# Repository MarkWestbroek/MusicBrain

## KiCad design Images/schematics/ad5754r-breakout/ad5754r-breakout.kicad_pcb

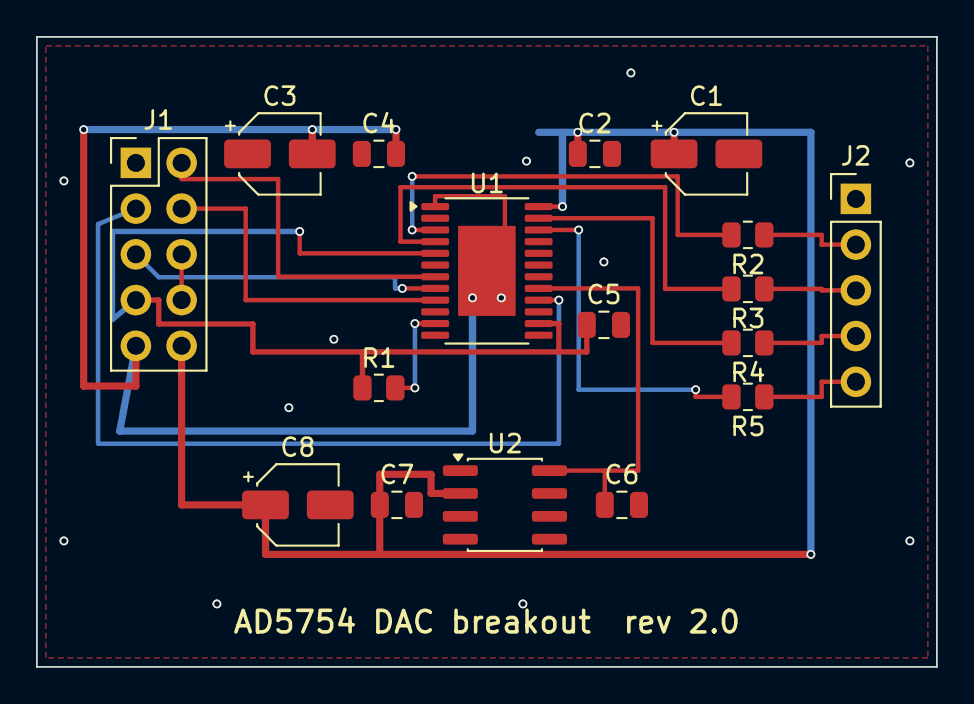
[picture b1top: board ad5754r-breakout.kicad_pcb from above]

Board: 2 copper layers, 50.0 x 35.0 mm, 17 parts (0 on the bottom side), 18 nets.

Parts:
C1, C3, C8: 10uF/25V; CP_Elec_4x5.3
C2, C4, C5, C6, C7: 100nF; C_0805_2012Metric
J1: SPI+Power; PinHeader_2x05_P2.54mm_Vertical
J2: GND+DAC A-D; PinHeader_1x05_P2.54mm_Vertical
R1: 10k; R_0805_2012Metric
R2, R3, R4, R5: 100R; R_0805_2012Metric
U1: AD5754BREZ; HTSSOP-24-1EP_4.4x7.8mm_P0.65mm_EP3.2x5mm
U2: ADR421; SOIC-8_3.9x4.9mm_P1.27mm

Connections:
+3V3: C5.1, J1.7, R1.1, U1.5, U1.14
+12V: C1.1, C2.1, C7.1, C8.1, J1.10, U1.24, U2.2
-12V: C3.2, C4.2, J1.9, U1.1, U1.25
/SCLK: J1.5, U1.8
/SDIN: J1.4, U1.9
/SDO: J1.3, U1.16
/SYNC: J1.2, U1.7
/VOUTA: R2.2, U1.3
/VOUTB: R3.2, U1.4
/VOUTC: R4.2, U1.23
/VOUTD: R5.2, U1.22
/VREF: C6.1, U1.17, U2.8
GND: C1.2, C2.2, C3.1, C4.1, C5.2, C6.2, C7.2, C8.2, J1.1, J1.6, J1.8, J2.1, U1.10, U1.15, U1.18, U1.19, U1.20, U1.21, U2.4
unnamed: J2.2, R2.1
unnamed: J2.3, R3.1
unnamed: J2.4, R4.1
unnamed: J2.5, R5.1
unnamed: R1.2, U1.11

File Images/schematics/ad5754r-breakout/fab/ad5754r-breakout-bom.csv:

"Comment","Designator","Footprint","Qty","LCSC Part #"
"10uF/25V","C1,C3,C8","Capacitor_SMD:CP_Elec_4x5.3","3",""
"100nF","C2,C4-C7","Capacitor_SMD:C_0805_2012Metric","5",""
"SPI+Power","J1","Connector_PinHeader_2.54mm:PinHeader_2x05_P2.54mm_Vertical","1",""
"GND+DAC A-D","J2","Connector_PinHeader_2.54mm:PinHeader_1x05_P2.54mm_Vertical","1",""
"10k","R1","Resistor_SMD:R_0805_2012Metric","1",""
"100R","R2-R5","Resistor_SMD:R_0805_2012Metric","4",""
"AD5754BREZ","U1","Package_SO:HTSSOP-24-1EP_4.4x7.8mm_P0.65mm_EP3.2x5mm","1",""
"ADR421","U2","Package_SO:SOIC-8_3.9x4.9mm_P1.27mm","1",""

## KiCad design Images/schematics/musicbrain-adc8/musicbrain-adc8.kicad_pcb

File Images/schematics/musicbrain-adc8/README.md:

# MusicBrain ADC8 — 8× CV-ingang (slotkaart)

**Status**: v1.1 — schema ERC-schoon + netlist geverifieerd; PCB **volledig
geroute** (DRC 0 fouten, 0 unconnected).
**Spec**: `doc/spi-bus-spec.md`. Bord: 40 mm breed × **80 mm hoog**
(standaard-kaarthoogte H voor de gedeelde bovenplaat), 2 lagen.

## Wat het is

8 CV-ingangen op een **AD7606** (16-bit SAR, 8 kanalen simultaan gesampled):
±10V of ±5V **rechtstreeks de chip in** — 1 MΩ ingangsimpedantie en interne
clamps, dus géén opamp-frontend per kanaal. Keuze overgenomen van Nic
Newdigate's teensy-eurorack-breakout (met toestemming); de pinout is tegen
zijn bewezen ontwerp geverifieerd.

## Busaansluiting (seriële mode)

| AD7606 | Buslijn | Toelichting |
|---|---|---|
| ~RD/SCLK, ~CS | SCLK, CS | seriële uitlezing |
| DOUTA | MISO | 8×16 bit achter elkaar; DOUTB ongebruikt (nc) |
| CONVST A+B (gekoppeld) | **SPARE1 = CONVST** | busbrede "sample nú"-strobe — alle ADC-kaarten samplen synchroon |
| BUSY | IRQ (slotpin 16) | hoog tijdens conversie (~4 µs); dalende flank = data klaar → interrupt |
| RESET | **SPARE2 = ADC_RESET** | resetpuls na power-up, firmware-gestuurd; 100k pulldown (R9) op de kaart |
| PAR/~SER, ~STBY, REF_SELECT | +3V3 | serieel, actief, interne 2,5V-referentie |
| RANGE | JP1 | jumper: +3V3 = ±10V, GND = ±5V |
| OS0..2, DB0-6, DB9-15 | GND | geen oversampling; parallelle databus plat |

Firmware-cyclus: CONVST-puls → wacht op IRQ (BUSY↓) → CS laag → 8×16 bit
klokken via MISO → CS hoog.

## Voeding & ondersteuning

- AVCC = 5V **lokaal** (AMS1117-5.0 uit +12V, zoals op de gate-kaart);
  VDRIVE = +3V3 van de bus, zodat de logica op busniveau praat.
- REGCAP ×2 (1 µF), REFCAPA/B gekoppeld (10 µF), REFIN/REFOUT (10 µF) —
  de voorgeschreven ondersteuning voor de interne referentie.
- 1 kΩ serie in alle acht ingangen (bescherming); VxGND-pinnen aan het
  GND-vlak.

## Aansluitingen

- **J1** (haakse male 2×10, onderrand): bus-slotcontract; MOSI/LDAC/SDA/SCL nc.
- **J2** (haakse male 1×10, bovenrand, recht boven het midden van J1):
  1 = GND, 2–9 = IN1..8, 10 = GND — **identiek contract als GATE8-J2**,
  dus hetzelfde jack8-printje past.
- **JP1** (1×3): RANGE-keuze ±10V / ±5V.

## PCB-notities (v1.1)

De volgorde-omkering tussen de chip-ingangen (V1 oost … V8 west op de
noordrij) en het J2-contract (IN1 west … IN8 oost) is opgelost met
**Manhattan-routing**: F.Cu draagt uitsluitend verticalen (escape onder elk
V-pad, drop naar elke serieweerstand), B.Cu draagt acht horizontale lanes
(y 118,4–124,0, steek 0,8 mm) — zo kruist niets op dezelfde laag. De
SPI/stuur-lijnen bereiken de westkolom van de chip via zes F-verticalen
("diepste entry → oostelijkste verticaal"), gevoed vanaf J1 via korte
B-lanes onderin. De GND-pads tussen de V-escapes hangen aan een eigen
verzamelrail (y 130,5) met via's naar het B-vlak.

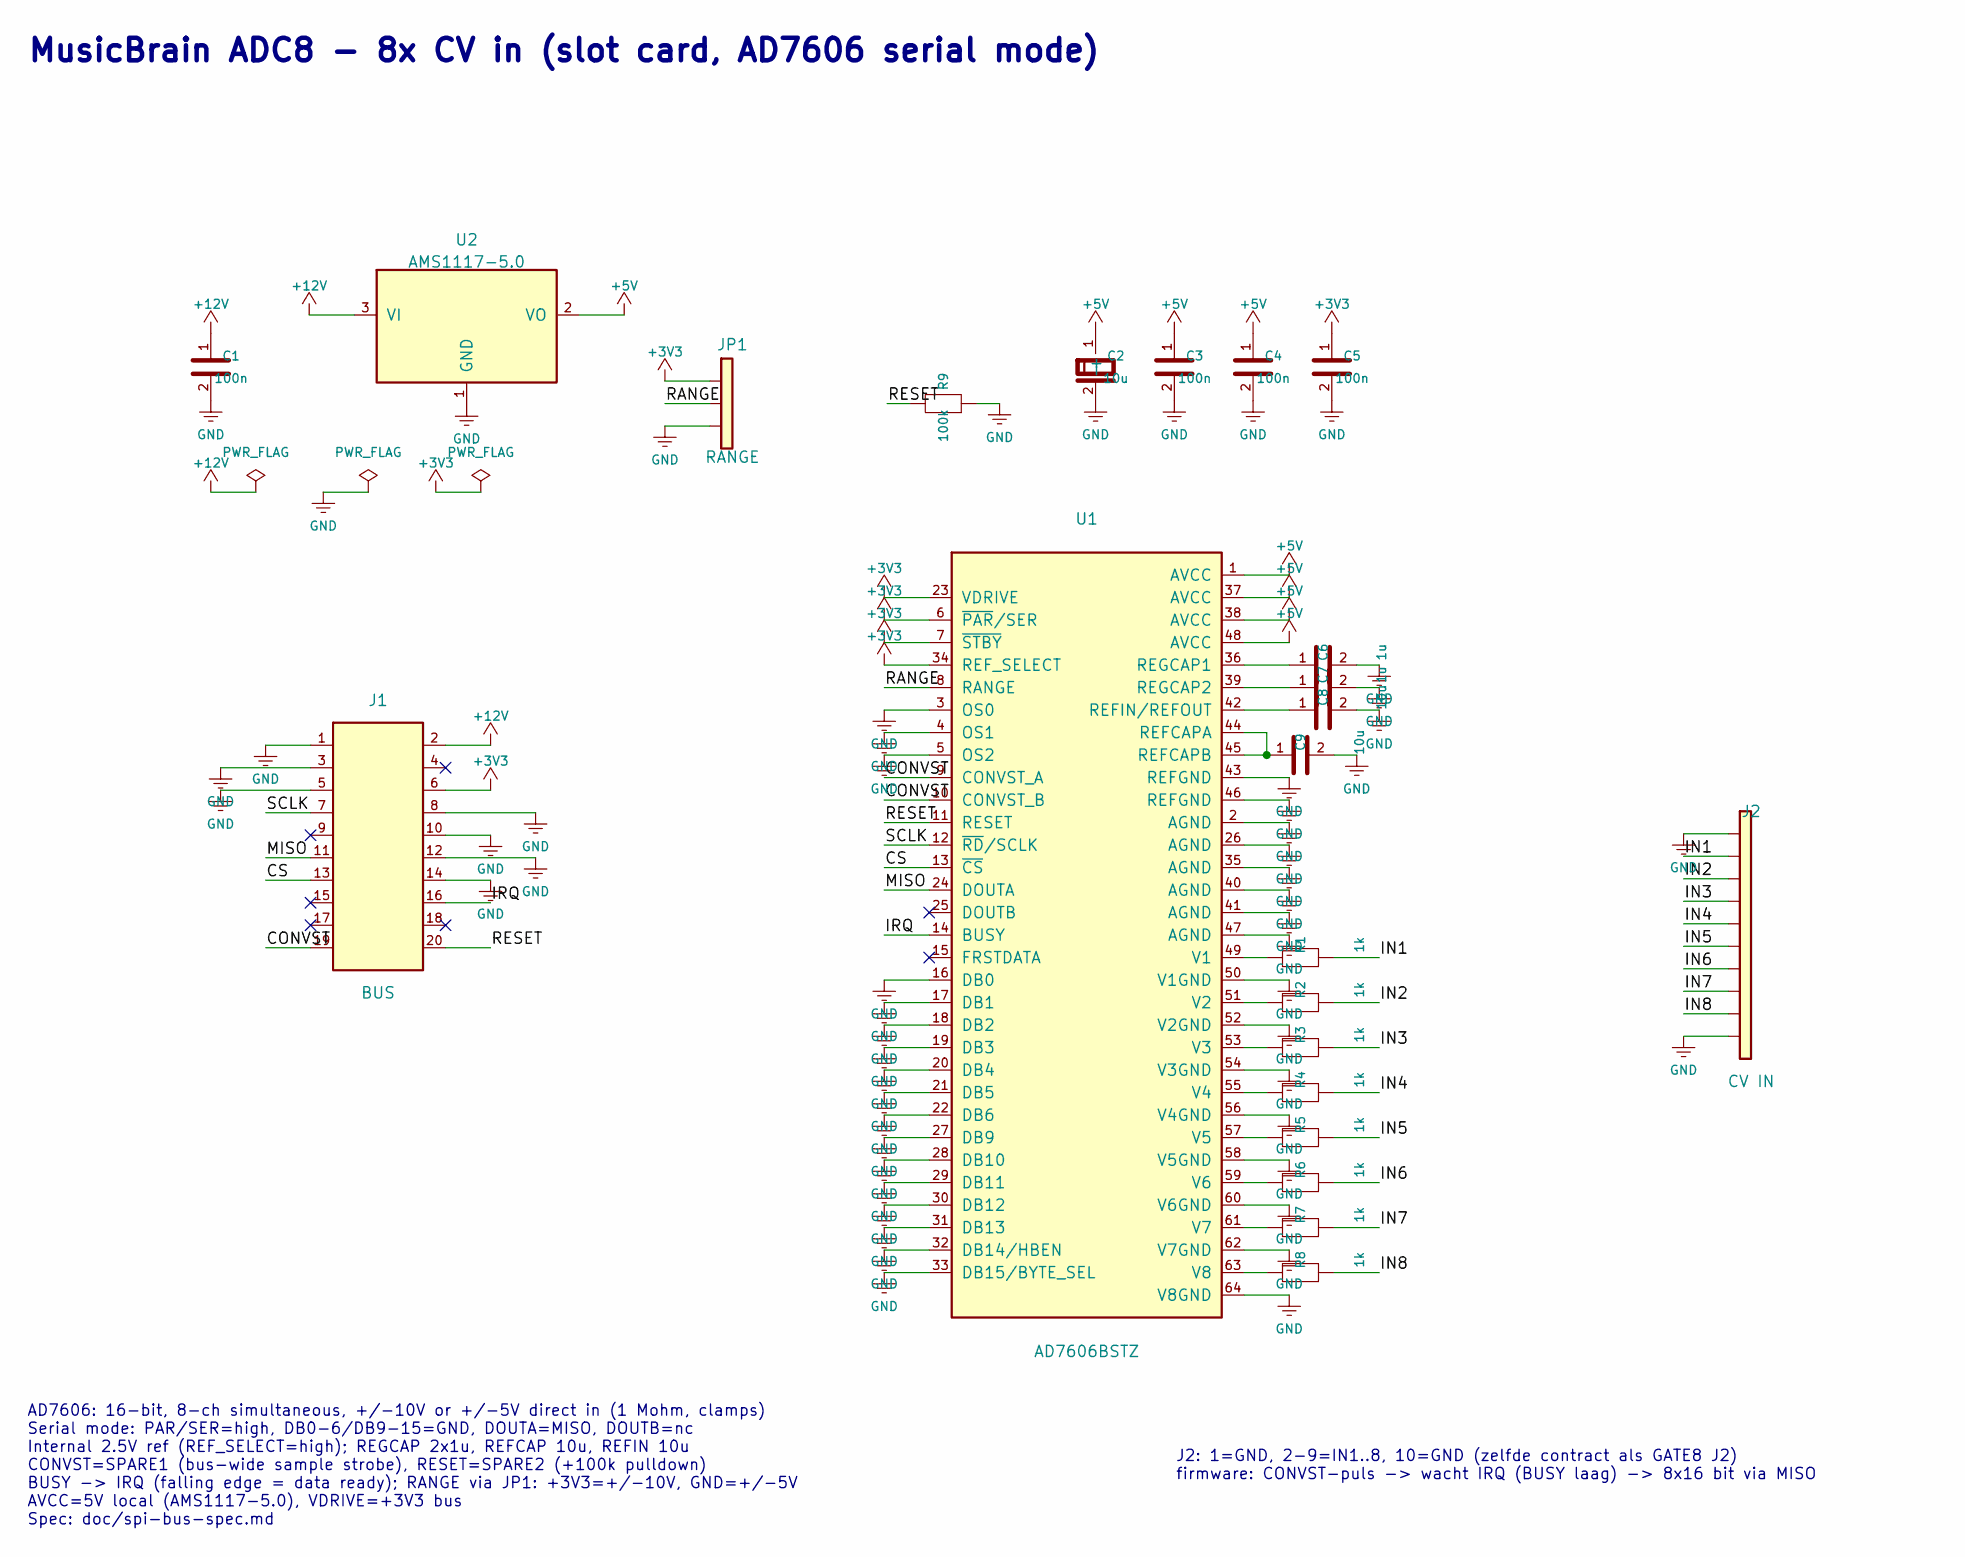
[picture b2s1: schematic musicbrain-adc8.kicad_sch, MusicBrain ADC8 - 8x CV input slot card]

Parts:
C1, C3, C4, C5: 100n; C_0805_2012Metric
C2: 10u; CP_Elec_4x5.3
C6, C7: 1u; C_0805_2012Metric
C8, C9: 10u; C_0805_2012Metric
J1: BUS; PinHeader_2x10_P2.54mm_Horizontal
J2: CV IN; PinHeader_1x10_P2.54mm_Horizontal
JP1: RANGE; PinHeader_1x03_P2.54mm_Vertical
R1, R2, R3, R4, R5, R6, R7, R8: 1k; R_0805_2012Metric
R9: 100k; R_0805_2012Metric
U1: AD7606BSTZ; LQFP-64_10x10mm_P0.5mm
U2: AMS1117-5.0; SOT-223-3_TabPin2

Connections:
+3V3: C5.1, J1.6, JP1.1, U1.6 (~PAR/SER), U1.7 (~STBY), U1.23 (VDRIVE), U1.34 (REF_SELECT)
+5V: C2.1 (+), C3.1, C4.1, U1.1 (AVCC), U1.37 (AVCC), U1.38 (AVCC), U1.48 (AVCC), U2.2 (VO)
+12V: C1.1, J1.2, U2.3 (VI)
/CONVST: J1.19, U1.9 (CONVST_A), U1.10 (CONVST_B)
/CS: J1.13, U1.13 (~CS)
/IN1: J2.2, R1.2
/IN2: J2.3, R2.2
/IN3: J2.4, R3.2
/IN4: J2.5, R4.2
/IN5: J2.6, R5.2
/IN6: J2.7, R6.2
/IN7: J2.8, R7.2
/IN8: J2.9, R8.2
/IRQ: J1.16, U1.14 (BUSY)
/MISO: J1.11, U1.24 (DOUTA)
/RANGE: JP1.2, U1.8 (RANGE)
/RESET: J1.20, R9.1, U1.11 (RESET)
/SCLK: J1.7, U1.12 (~RD/SCLK)
GND: C1.2, C2.2 (-), C3.2, C4.2, C5.2, C6.2, C7.2, C8.2, C9.2, J1.1, J1.3, J1.5, J1.8, J1.10, J1.12, J1.14, J2.1, J2.10, JP1.3, R9.2, U1.2 (AGND), U1.3 (OS0), U1.4 (OS1), U1.5 (OS2), U1.16 (DB0), U1.17 (DB1), U1.18 (DB2), U1.19 (DB3), U1.20 (DB4), U1.21 (DB5), U1.22 (DB6), U1.26 (AGND), U1.27 (DB9), U1.28 (DB10), U1.29 (DB11), U1.30 (DB12), U1.31 (DB13), U1.32 (DB14/HBEN), U1.33 (DB15/BYTE_SEL), U1.35 (AGND), U1.40 (AGND), U1.41 (AGND), U1.43 (REFGND), U1.46 (REFGND), U1.47 (AGND), U1.50 (V1GND), U1.52 (V2GND), U1.54 (V3GND), U1.56 (V4GND), U1.58 (V5GND), U1.60 (V6GND), U1.62 (V7GND), U1.64 (V8GND), U2.1 (GND)
unnamed: C9.1, U1.44 (REFCAPA), U1.45 (REFCAPB)
unnamed: C8.1, U1.42 (REFIN/REFOUT)
unnamed: C6.1, U1.36 (REGCAP1)
unnamed: C7.1, U1.39 (REGCAP2)
unnamed: R1.1, U1.49 (V1)
unnamed: R2.1, U1.51 (V2)
unnamed: R3.1, U1.53 (V3)
unnamed: R4.1, U1.55 (V4)
unnamed: R5.1, U1.57 (V5)
unnamed: R6.1, U1.59 (V6)
unnamed: R7.1, U1.61 (V7)
unnamed: R8.1, U1.63 (V8)

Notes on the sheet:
MusicBrain ADC8 - 8x CV in (slot card, AD7606 serial mode)
AD7606: 16-bit, 8-ch simultaneous, +/-10V or +/-5V direct in (1 Mohm, clamps) Serial mode: PAR/SER=high, DB0-6/DB9-15=GND, DOUTA=MISO, DOUTB=nc Internal 2.5V ref (REF_SELECT=high); REGCAP 2x1u, REFCAP 10u, REFIN 10u CONVST=SPARE1 (bus-wide sample strobe), RESET=SPARE2 (+100k pulldown) BUSY -> IRQ (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
J2: 1=GND, 2-9=IN1..8, 10=GND (zelfde contract als GATE8 J2) firmware: CONVST-puls -> wacht IRQ (BUSY laag) -> 8x16 bit via MISO

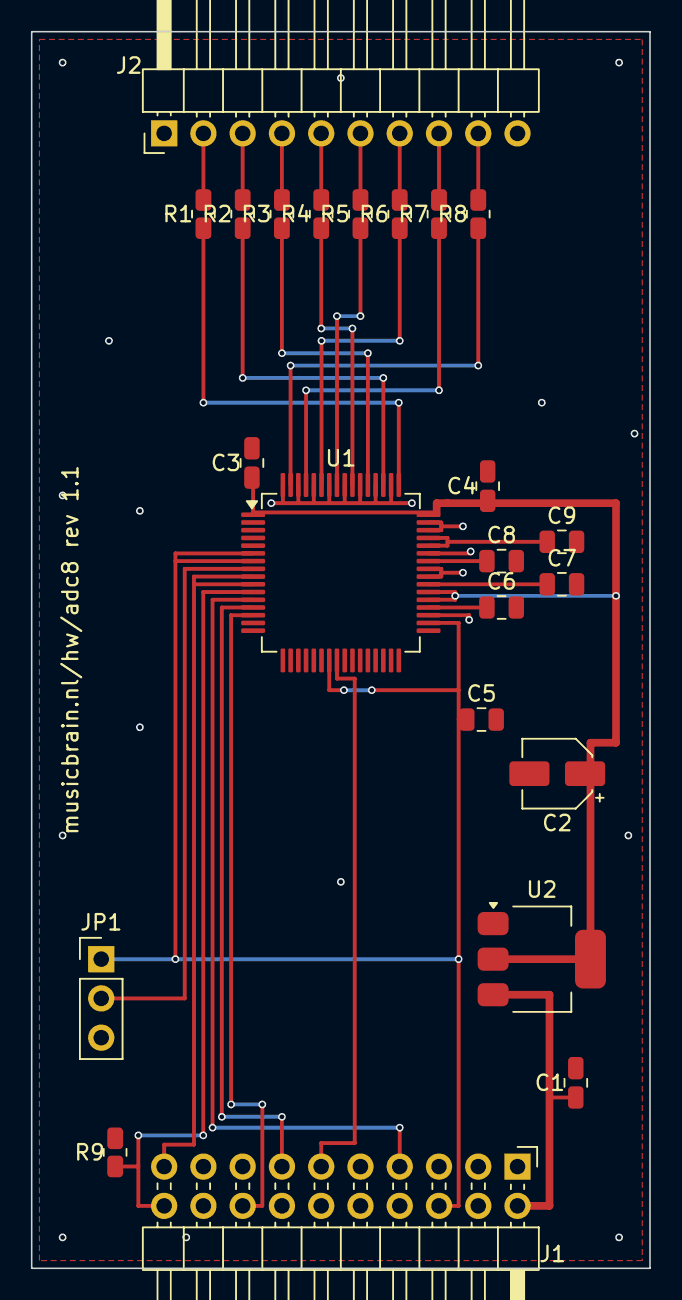
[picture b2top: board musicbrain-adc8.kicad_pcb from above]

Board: 2 copper layers, 40.0 x 80.0 mm, 23 parts (0 on the bottom side), 31 nets.

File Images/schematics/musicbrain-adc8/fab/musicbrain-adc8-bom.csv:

"Comment","Designator","Footprint","Qty","LCSC Part #"
"100n","C1,C3-C5","Capacitor_SMD:C_0805_2012Metric","4",""
"10u","C2","Capacitor_SMD:CP_Elec_4x5.3","1",""
"1u","C6,C7","Capacitor_SMD:C_0805_2012Metric","2",""
"10u","C8,C9","Capacitor_SMD:C_0805_2012Metric","2",""
"BUS","J1","Connector_PinHeader_2.54mm:PinHeader_2x10_P2.54mm_Horizontal","1",""
"CV IN","J2","Connector_PinHeader_2.54mm:PinHeader_1x10_P2.54mm_Horizontal","1",""
"RANGE","JP1","Connector_PinHeader_2.54mm:PinHeader_1x03_P2.54mm_Vertical","1",""
"1k","R1-R8","Resistor_SMD:R_0805_2012Metric","8",""
"100k","R9","Resistor_SMD:R_0805_2012Metric","1",""
"AD7606BSTZ","U1","Package_QFP:LQFP-64_10x10mm_P0.5mm","1",""
"AMS1117-5.0","U2","Package_TO_SOT_SMD:SOT-223-3_TabPin2","1",""

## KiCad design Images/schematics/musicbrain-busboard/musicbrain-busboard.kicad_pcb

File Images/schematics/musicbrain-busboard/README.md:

# MusicBrain busboard — Teensy 4.1 backplane

**Status**: schema ERC-schoon; PCB volledig geroute (DRC 0 fouten, 0 unconnected).
**Leidende spec**: `doc/spi-bus-spec.md`. Bestanden: `.kicad_sch` / `.kicad_pcb`, PDF's ernaast.

## Wat het is

De ruggengraat van het systeem: een 200×115 mm backplane met een Teensy 4.1
(op twee 1×24 socketstrips), **6 verticale kaartslots** (2×10 pinsocket) en
**2 hub-headers** (2×5 IDC) waar bestaande breakouts via lintkabel op
aansluiten. Voeding komt binnen als Eurorack ±12V; het bord maakt daar zelf
+5V (R-78E5.0 buck) en +3V3 (AMS1117) van.

## Signaalarchitectuur

| Groep | Lijnen | Teensy-pin | Toelichting |
|---|---|---|---|
| SPI | SCLK / MOSI / MISO | 13 / 11 / 12 | gedeeld door alle slots + hubs; slaves laten MISO los als hun CS hoog is |
| Chip-selects | CS1..CS6 → slot 1..6 | 10, 9, 8, 7, 6, 5 | **directe GPIO's**, één per slot ("geografisch": elke kaart ziet zijn CS op connectorpin 13) |
| | CS7, CS8 → hub 1, 2 | 4, 3 | vast bedraad naar pin 2 (SYNC) van de hub-headers |
| Interrupts | IRQ1..IRQ6 → slot 1..6 | 28..33 | directe GPIO-ingangen, interrupt-capable; kaart meldt "data klaar" op connectorpin 16 |
| Sync-strobes | LDAC | 2 | alle DAC-kaarten updaten hun uitgangen tegelijk op LDAC↓ |
| | SPARE1 (= CONVST) | 40 | alle ADC-kaarten samplen tegelijk (spiegelbeeld van LDAC) |
| | SPARE2 (= ADC_RESET) | 41 | busbrede reset voor AD7606-kaarten; vrij voor andere kaarten |
| I2C | SDA / SCL | 18 / 19 | voor trage kaarten (pots/encoders/OLED); pull-ups 2k2 op het busboard |
| Voeding | +12V / −12V / +3V3 | — | +3V3 komt van de AMS1117, **niet** van de Teensy-regulator |

Signaalintegriteit: **33 Ω serieweerstanden (R1/R2) in SCLK en MOSI**, direct
bij de Teensy — serieterminatie die reflecties op de multidrop-bus dempt.
Start de firmware op 2–4 MHz SPI; opvoeren kan daarna.

## PCB-opbouw (hoe de routing in elkaar zit)

- **B.Cu (onderlaag): 28 horizontale "buslanen"** op y = 68…104,5 mm — van
  boven naar beneden: LDAC, MOSI, MISO, SCLK, SDA, SCL, SPARE1, SPARE2,
  +3V3 (0,5 mm), +12V en −12V (0,8 mm), +5V, dan CS1..CS8 en IRQ1..IRQ6.
  CS/IRQ-lanen lopen alleen zo ver oostwaarts als hun slot — daar zie je de
  "trappetjes" in de PDF.
- **F.Cu (bovenlaag): verticale aftakkingen.** Elk slot heeft rechts een eigen
  kanaal (13 sporen op 1 mm steek) dat de connectorpinnen via een via op de
  juiste laan prikt. De Teensy heeft links zijn eigen fan-out (26 signalen);
  de volgorde van de verticalen is zo gekozen dat niets elkaar kruist.
- **Hubs**: J7 (noord) waaiert naar beneden zijn lanen op, J8 (zuid) naar
  boven; J8 zit bewust onder de lanenbundel — zo blijft alles kruisingsvrij.
- **Voeding**: de ±12V van J9 steekt op F.Cu tussen de Teensy-padrijen door
  ("mid-rij-oversteek") naar de +12V/−12V-lanen; de +5V loopt als aparte laan
  van Teensy-VIN en de R-78E naar de ontkoppelrij (C1–C8, onderrand).
- **GND**: geen sporen — massieve vlakken op beide lagen (solid connect),
  15 stitching-via's.

## Aandachtspunten

- **Teensy VIN hangt aan de +5V-rail.** Wil je USB en busvoeding tegelijk:
  snij de VUSB/VIN-brug op de Teensy door (standaard PJRC-advies).
- De Teensy-footprint is custom (`MusicBrain:Teensy41_THT`): 48 THT-pads,
  0,6" rijafstand, nummering tegen de klok in — pin 1 linksboven bij de USB.
- Slots zijn PinSocket 2×10 (female); kaarten hebben male headers. Let op:
  de socket-footprint spiegelt kolom 2 naar links.
- Hot-pluggen van kaarten: niet doen (ongebufferde bus).

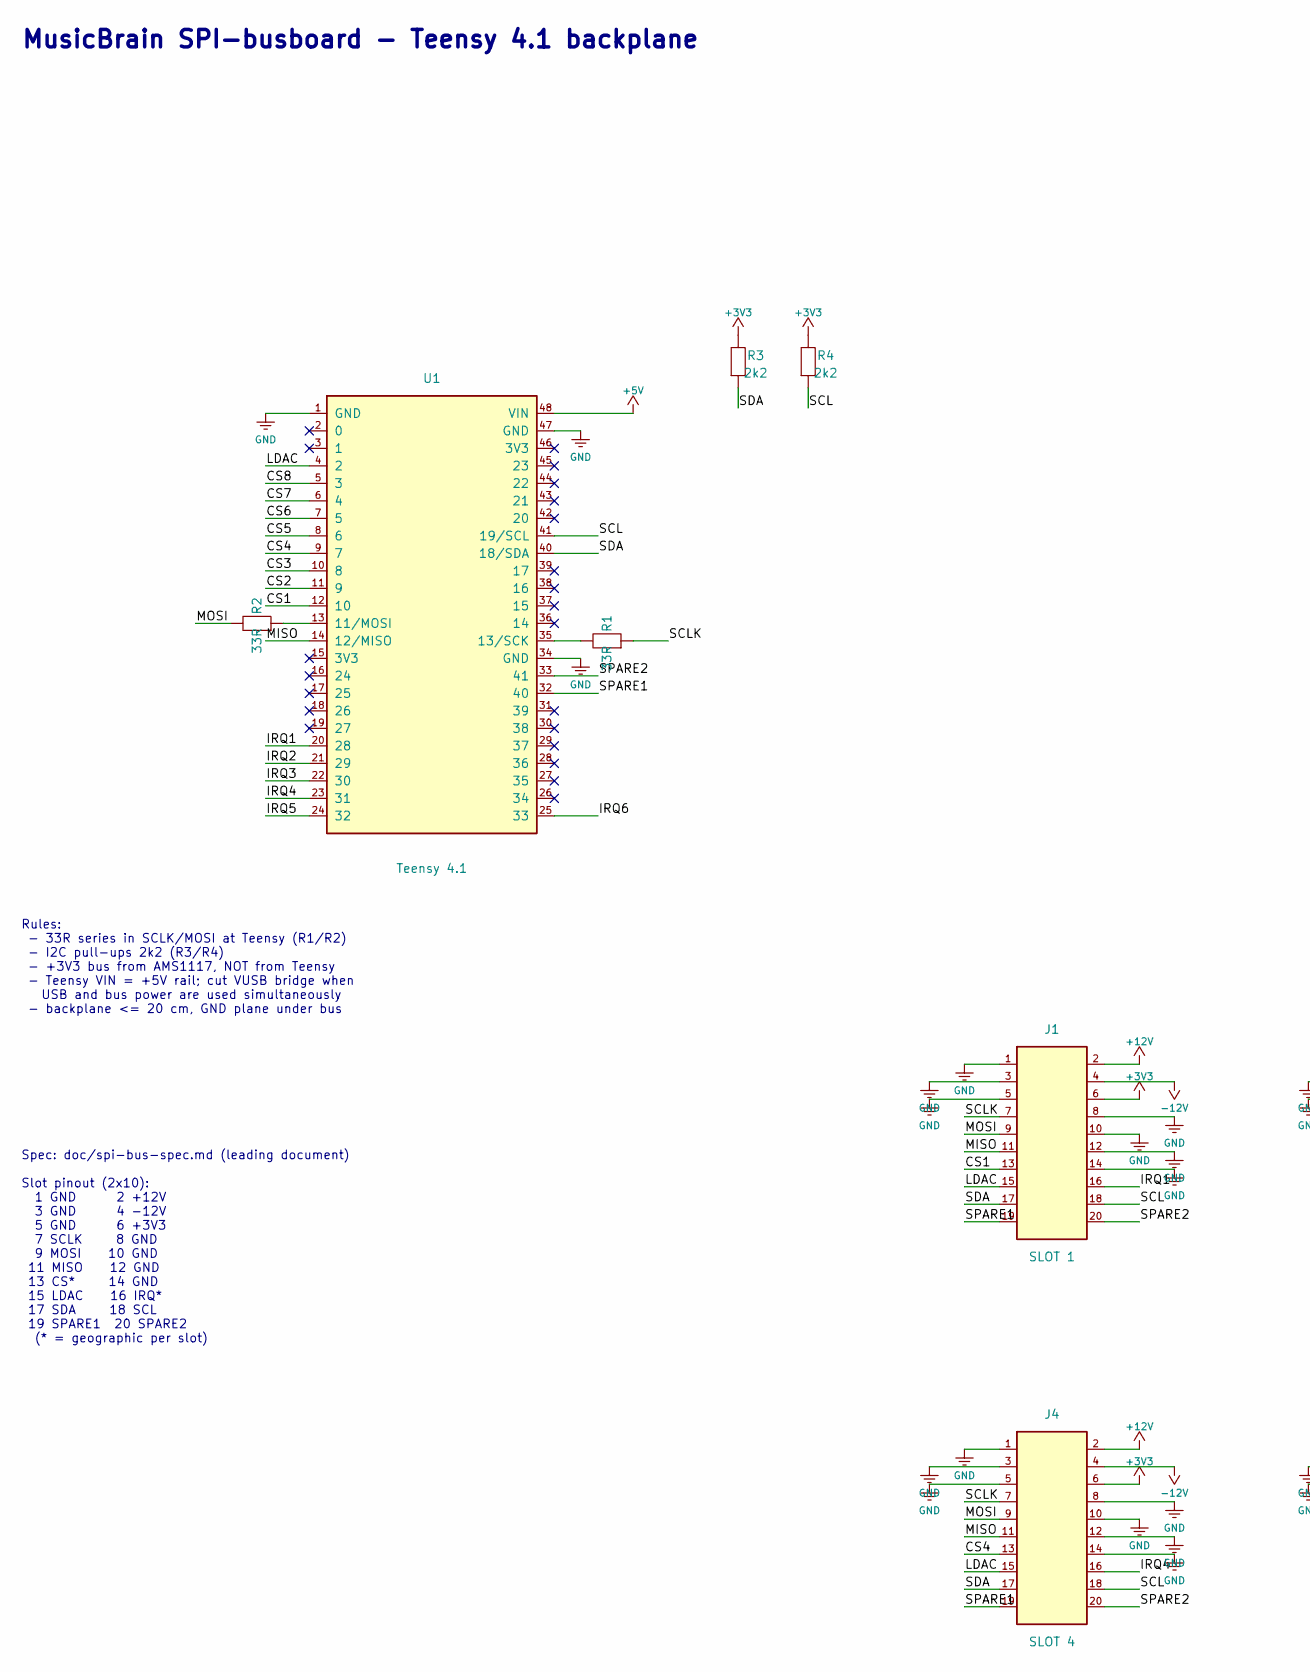
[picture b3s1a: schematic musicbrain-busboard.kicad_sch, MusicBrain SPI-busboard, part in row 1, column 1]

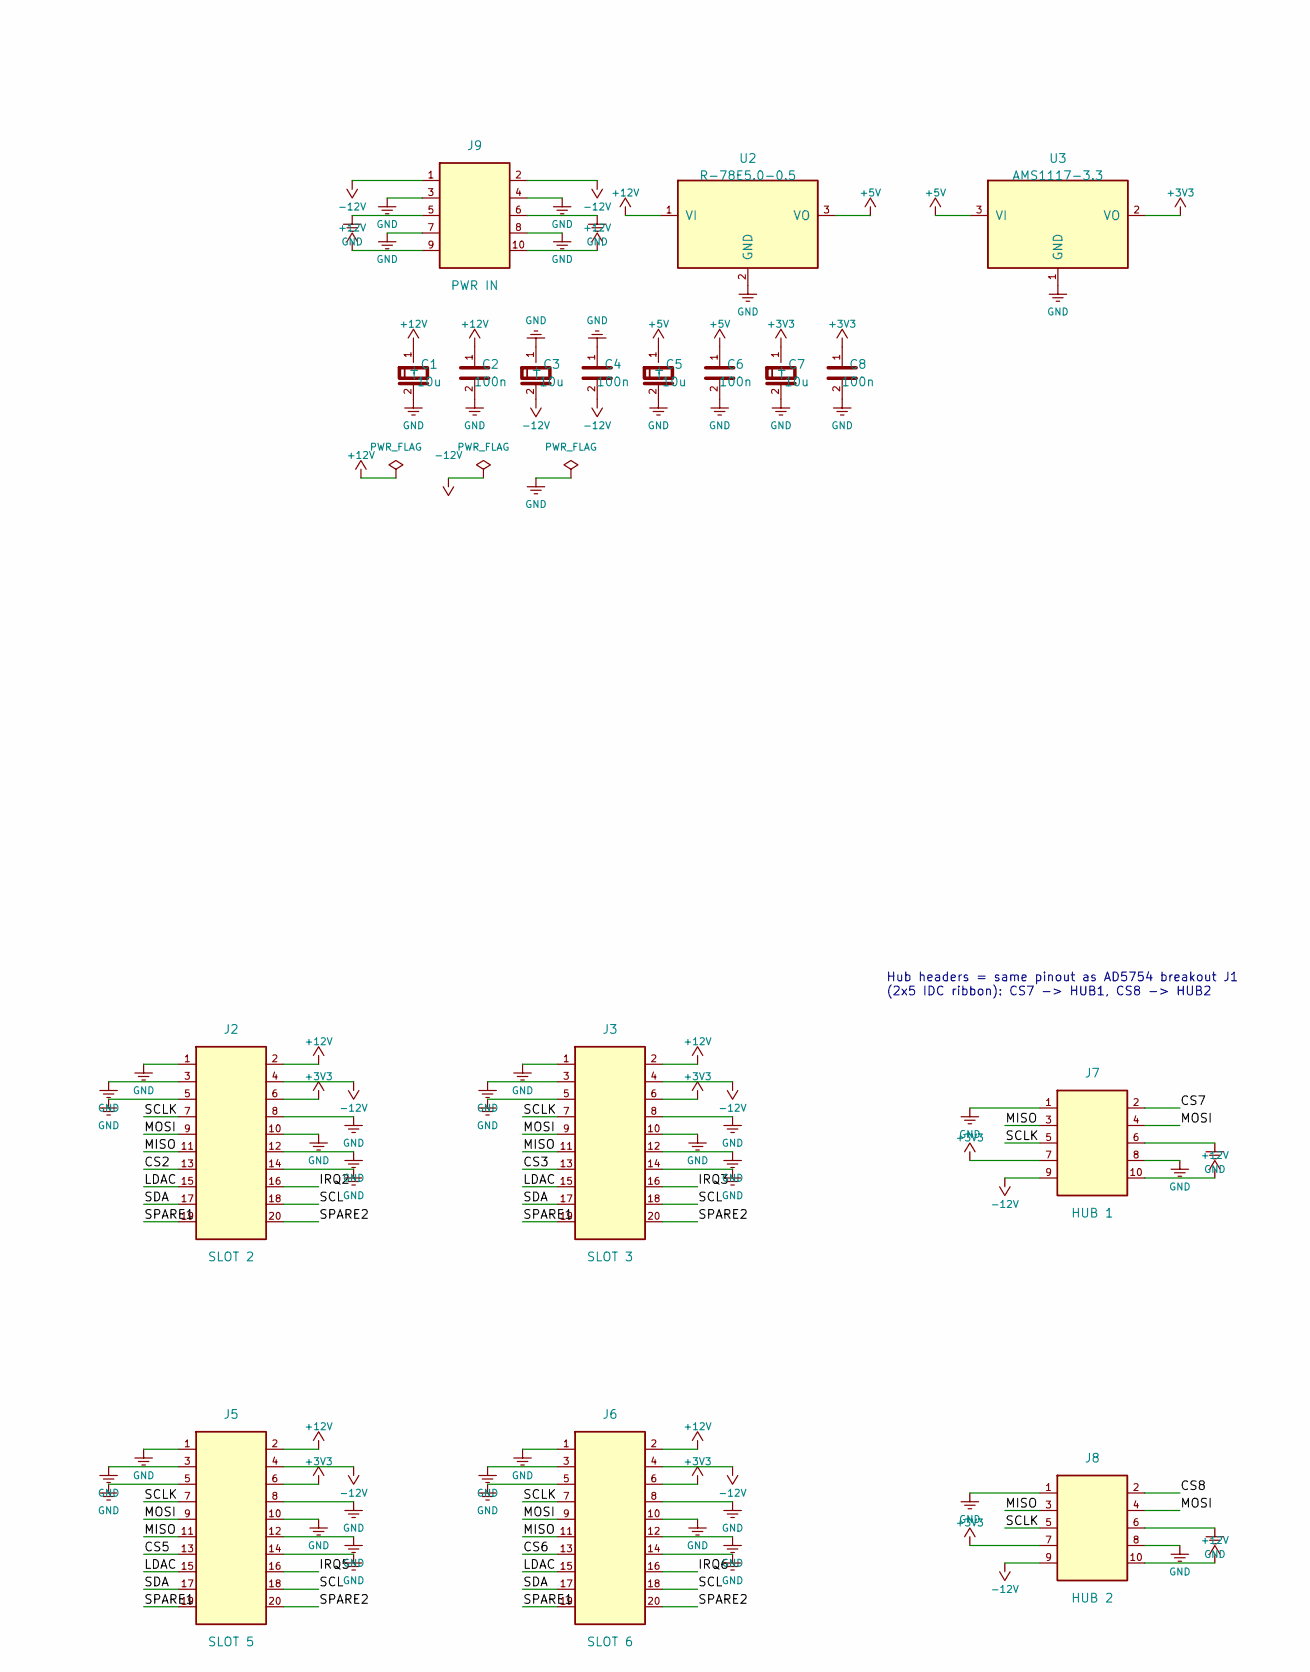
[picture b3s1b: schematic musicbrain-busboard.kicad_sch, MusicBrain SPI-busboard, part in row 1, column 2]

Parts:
C1, C3, C5, C7: 10u; CP_Elec_4x5.3
C2, C4, C6, C8: 100n; C_0805_2012Metric
J1: SLOT 1; PinSocket_2x10_P2.54mm_Vertical
J2: SLOT 2; PinSocket_2x10_P2.54mm_Vertical
J3: SLOT 3; PinSocket_2x10_P2.54mm_Vertical
J4: SLOT 4; PinSocket_2x10_P2.54mm_Vertical
J5: SLOT 5; PinSocket_2x10_P2.54mm_Vertical
J6: SLOT 6; PinSocket_2x10_P2.54mm_Vertical
J7: HUB 1; IDC-Header_2x05_P2.54mm_Vertical
J8: HUB 2; IDC-Header_2x05_P2.54mm_Vertical
J9: PWR IN; IDC-Header_2x05_P2.54mm_Vertical
R1, R2: 33R; R_0805_2012Metric
R3, R4: 2k2; R_0805_2012Metric
U1: Teensy 4.1
U2: R-78E5.0-0.5; Converter_DCDC_RECOM_R-78E-0.5_THT
U3: AMS1117-3.3; SOT-223-3_TabPin2

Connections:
+3V3: C7.1 (+), C8.1, J1.6, J2.6, J3.6, J4.6, J5.6, J6.6, J7.7, J8.7, R3.1, R4.1, U3.2 (VO)
+5V: C5.1 (+), C6.1, U1.48 (VIN), U2.3 (VO), U3.3 (VI)
+12V: C1.1 (+), C2.1, J1.2, J2.2, J3.2, J4.2, J5.2, J6.2, J7.10, J8.10, J9.9, J9.10, U2.1 (VI)
-12V: C3.2 (-), C4.2, J1.4, J2.4, J3.4, J4.4, J5.4, J6.4, J7.9, J8.9, J9.1, J9.2
/CS1: J1.13, U1.12 (10)
/CS2: J2.13, U1.11 (9)
/CS3: J3.13, U1.10 (8)
/CS4: J4.13, U1.9 (7)
/CS5: J5.13, U1.8 (6)
/CS6: J6.13, U1.7 (5)
/CS7: J7.2, U1.6 (4)
/CS8: J8.2, U1.5 (3)
/IRQ1: J1.16, U1.20 (28)
/IRQ2: J2.16, U1.21 (29)
/IRQ3: J3.16, U1.22 (30)
/IRQ4: J4.16, U1.23 (31)
/IRQ5: J5.16, U1.24 (32)
/IRQ6: J6.16, U1.25 (33)
/LDAC: J1.15, J2.15, J3.15, J4.15, J5.15, J6.15, U1.4 (2)
/MISO: J1.11, J2.11, J3.11, J4.11, J5.11, J6.11, J7.3, J8.3, U1.14 (12/MISO)
/MOSI: J1.9, J2.9, J3.9, J4.9, J5.9, J6.9, J7.4, J8.4, R2.1
/SCL: J1.18, J2.18, J3.18, J4.18, J5.18, J6.18, R4.2, U1.41 (19/SCL)
/SCLK: J1.7, J2.7, J3.7, J4.7, J5.7, J6.7, J7.5, J8.5, R1.2
/SDA: J1.17, J2.17, J3.17, J4.17, J5.17, J6.17, R3.2, U1.40 (18/SDA)
/SPARE1: J1.19, J2.19, J3.19, J4.19, J5.19, J6.19, U1.32 (40)
/SPARE2: J1.20, J2.20, J3.20, J4.20, J5.20, J6.20, U1.33 (41)
GND: C1.2 (-), C2.2, C3.1 (+), C4.1, C5.2 (-), C6.2, C7.2 (-), C8.2, J1.1, J1.3, J1.5, J1.8, J1.10, J1.12, J1.14, J2.1, J2.3, J2.5, J2.8, J2.10, J2.12, J2.14, J3.1, J3.3, J3.5, J3.8, J3.10, J3.12, J3.14, J4.1, J4.3, J4.5, J4.8, J4.10, J4.12, J4.14, J5.1, J5.3, J5.5, J5.8, J5.10, J5.12, J5.14, J6.1, J6.3, J6.5, J6.8, J6.10, J6.12, J6.14, J7.1, J7.6, J7.8, J8.1, J8.6, J8.8, J9.3, J9.4, J9.5, J9.6, J9.7, J9.8, U1.1 (GND), U1.34 (GND), U1.47 (GND), U2.2 (GND), U3.1 (GND)
unnamed: R2.2, U1.13 (11/MOSI)
unnamed: R1.1, U1.35 (13/SCK)

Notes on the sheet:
MusicBrain SPI-busboard - Teensy 4.1 backplane
Spec: doc/spi-bus-spec.md (leading document) Slot pinout (2x10): 1 GND 2 +12V 3 GND 4 -12V 5 GND 6 +3V3 7 SCLK 8 GND 9 MOSI 10 GND 11 MISO 12 GND 13 CS* 14 GND 15 LDAC 16 IRQ* 17 SDA 18 SCL 19 SPARE1 20 SPARE2 (* = geographic per slot)
Rules: - 33R series in SCLK/MOSI at Teensy (R1/R2) - I2C pull-ups 2k2 (R3/R4) - +3V3 bus from AMS1117, NOT from Teensy - Teensy VIN = +5V rail; cut VUSB bridge when USB and bus power are used simultaneously - backplane <= 20 cm, GND plane under bus
Hub headers = same pinout as AD5754 breakout J1 (2x5 IDC ribbon): CS7 -> HUB1, CS8 -> HUB2

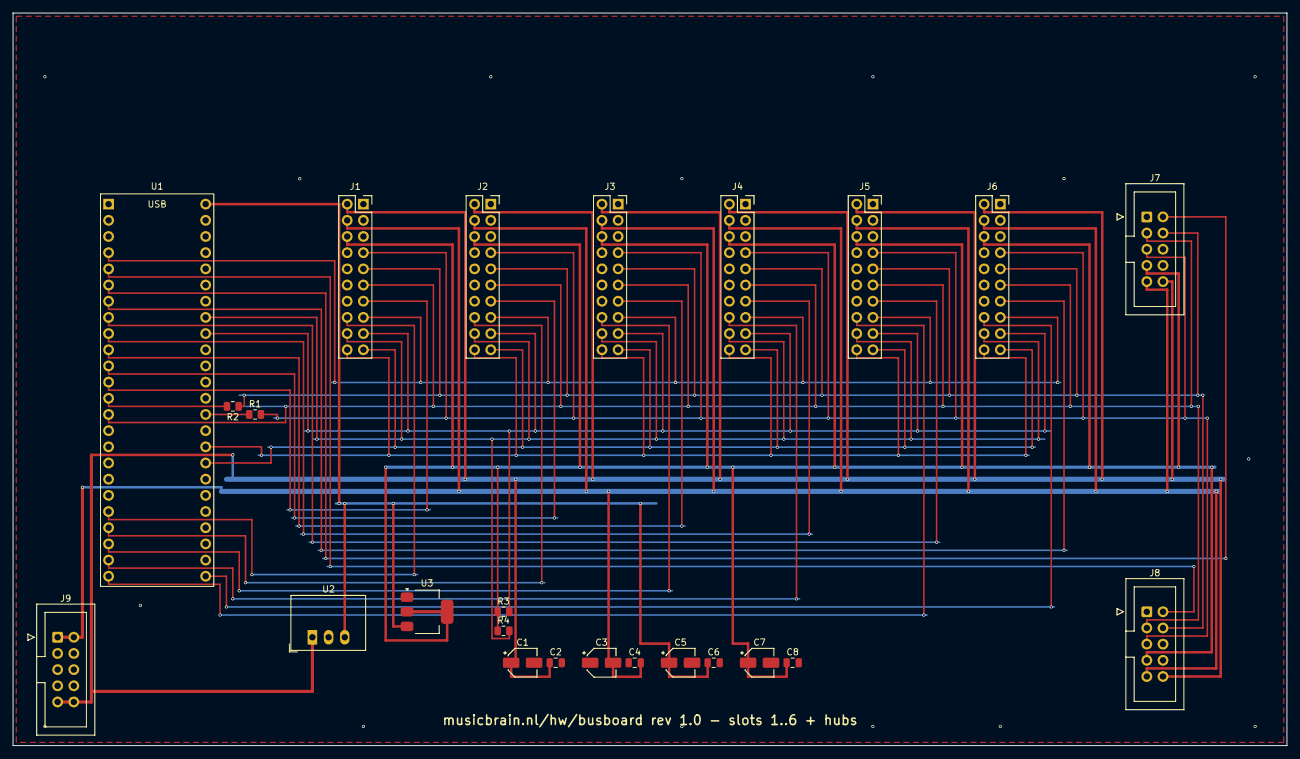
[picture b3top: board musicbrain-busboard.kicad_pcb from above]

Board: 2 copper layers, 200.0 x 115.0 mm, 24 parts (0 on the bottom side), 29 nets.

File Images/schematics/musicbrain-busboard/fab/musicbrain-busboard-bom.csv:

"Comment","Designator","Footprint","Qty","LCSC Part #"
"10u","C1,C3,C5,C7","Capacitor_SMD:CP_Elec_4x5.3","4",""
"100n","C2,C4,C6,C8","Capacitor_SMD:C_0805_2012Metric","4",""
"SLOT 1","J1","Connector_PinSocket_2.54mm:PinSocket_2x10_P2.54mm_Vertical","1",""
"SLOT 2","J2","Connector_PinSocket_2.54mm:PinSocket_2x10_P2.54mm_Vertical","1",""
"SLOT 3","J3","Connector_PinSocket_2.54mm:PinSocket_2x10_P2.54mm_Vertical","1",""
"SLOT 4","J4","Connector_PinSocket_2.54mm:PinSocket_2x10_P2.54mm_Vertical","1",""
"SLOT 5","J5","Connector_PinSocket_2.54mm:PinSocket_2x10_P2.54mm_Vertical","1",""
"SLOT 6","J6","Connector_PinSocket_2.54mm:PinSocket_2x10_P2.54mm_Vertical","1",""
"HUB 1","J7","Connector_IDC:IDC-Header_2x05_P2.54mm_Vertical","1",""
"HUB 2","J8","Connector_IDC:IDC-Header_2x05_P2.54mm_Vertical","1",""
"PWR IN","J9","Connector_IDC:IDC-Header_2x05_P2.54mm_Vertical","1",""
"EXP","J10","Connector_PinHeader_2.54mm:PinHeader_2x07_P2.54mm_Vertical","1",""
"DISPLAY","J11","Connector_PinHeader_2.54mm:PinHeader_1x09_P2.54mm_Vertical","1",""
"QWIIC","J12","Connector_PinHeader_2.54mm:PinHeader_1x04_P2.54mm_Vertical","1",""
"33R","R1,R2","Resistor_SMD:R_0805_2012Metric","2",""
"2k2","R3,R4","Resistor_SMD:R_0805_2012Metric","2",""
"Teensy 4.1","U1","","1",""
"R-78E5.0-0.5","U2","Converter_DCDC:Converter_DCDC_RECOM_R-78E-0.5_THT","1",""
"AMS1117-3.3","U3","Package_TO_SOT_SMD:SOT-223-3_TabPin2","1",""

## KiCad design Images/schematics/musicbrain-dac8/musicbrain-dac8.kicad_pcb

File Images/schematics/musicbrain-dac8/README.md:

# MusicBrain DAC8 — 8× CV-uitgang (slotkaart)

**Status**: schema ERC-schoon + netlist geverifieerd; PCB volledig geroute
(DRC 0 fouten, 0 unconnected). **Spec**: `doc/spi-bus-spec.md`.
Bord: 50 mm breed × **80 mm hoog** (H-standaard), 2 lagen.

## Wat het is

8 nette CV-uitgangen uit **2× AD5754BREZ** (16-bit quad-DAC, ±10V-bereik)
met een gedeelde **ADR421**-referentie (2,5 V precisie) — hetzelfde
gevalideerde recept als de AD5754-breakout, nu als slotkaart in lijn met
GATE8/ADC8.

## Architectuur

- **Daisy-chain**: MOSI → U1.SDIN, U1.SDO → U2.SDIN, U2.SDO → MISO.
  Eén CS voor beide chips; de firmware klokt 48-bit frames (2×24) en
  bereikt beide DAC's in één transactie. U2.SDO is tri-state bij CS hoog.
- **LDAC = buslijn** (slotpin 15): beide chips laden hun uitgangsregisters
  tegelijk op LDAC↓ — en tegelijk met álle andere DAC-kaarten op de bus.
  Dat is precies waarvoor de LDAC-lijn in de spec bestaat.
- **Offset binary** (BIN/2sCOMP = pin 5 → +3V3), ~CLR (pin 11) met 10k
  pull-up (R1), DVCC (pin 14) = +3V3, DGND (pin 15) = GND, interne
  versterkers op ±12V (AVDD/AVSS), EP-pads aan AVSS.
- **~LDAC = pin 10** → de bus-LDAC-lijn (slotpin 15); pin 12/13 = NC.
  De AD5754-pinnummering is geverifieerd tegen de datasheet
  (`doc/data-sheets/AD5754BREZ data.md`), Nic Newdigate's ontwerp én het
  ComponentSearchEngine-symbool — drie onafhankelijke bronnen.
- **AD5754BREZ heeft géén interne referentie** (de "R" in de datasheet-titel
  slaat op de R-variant die dat wél heeft). Vandaar de **ADR421** (U3, 2,5 V
  precisie) → REFIN (pin 17) van beide chips, met **0,1 µF (C6) + 10 µF (C14)**
  ontkoppeling op VREF zoals de datasheet voorschrijft.
- 100 Ω serie per uitgang (R2–R9), kortsluitbescherming.

## Kanaaltoewijzing

| CV | DAC | | CV | DAC |
|---|---|---|---|---|
| CV1 | U1·B | | CV5 | U2·A |
| CV2 | U1·A | | CV6 | U2·B |
| CV3 | U1·C | | CV7 | U2·C |
| CV4 | U1·D | | CV8 | U2·D |

(CV1/CV2 verwisseld t.o.v. alfabetisch — routinggedreven; firmware-tabel.)

## Aansluitingen

- **J1** (haakse male 2×10, onderrand): volledig contract incl. +12V,
  −12V, +3V3, LDAC; MOSI én MISO in gebruik (daisy).
- **J2** (haakse male 1×10, bovenrand): 1 = GND, 2–9 = CV1..8, 10 = GND —
  zelfde jack8-contract; **JP1 op het jack8-printje OPEN laten** (outputs!).

## PCB-notities

De acht VOUT's verlaten de chips via korte F-escapes naar via's en lopen
als B.Cu-lanes (y 114,3–118,3, strikt genest) naar de serieweerstandsrij.
De stuursignalen dalen als B-rijen onderin (CS 168,6 / SCLK 169,4 /
MOSI 170,2 / CLR 162,4) naar F-verticalen die de 0,65 mm-westkolommen
in nesten ("diepste entry → oostelijkste verticaal"); LDAC heeft een
F-band op y 167,3 en stapt bij U1 van onderen de padkolom in. De
±12V/+3V3-verdeling loopt via een F-corridor (y 120,3/121,1) boven de
chips en B-banden (y 160,8/161,6) onderlangs. VREF loopt op B.Cu van de
ADR421 naar beide REFIN-pinnen. DGND-pads tussen de fijne entries hangen
aan eigen redding-via's.

## Firmware

Setup per chip (via de keten): power-up register (alle kanalen aan),
output range ±10V, BIN-coding. Daarna per sample: 2×24 bit data door de
keten schuiven, CS hoog, en LDAC↓ (buslijn) voor de synchrone update.

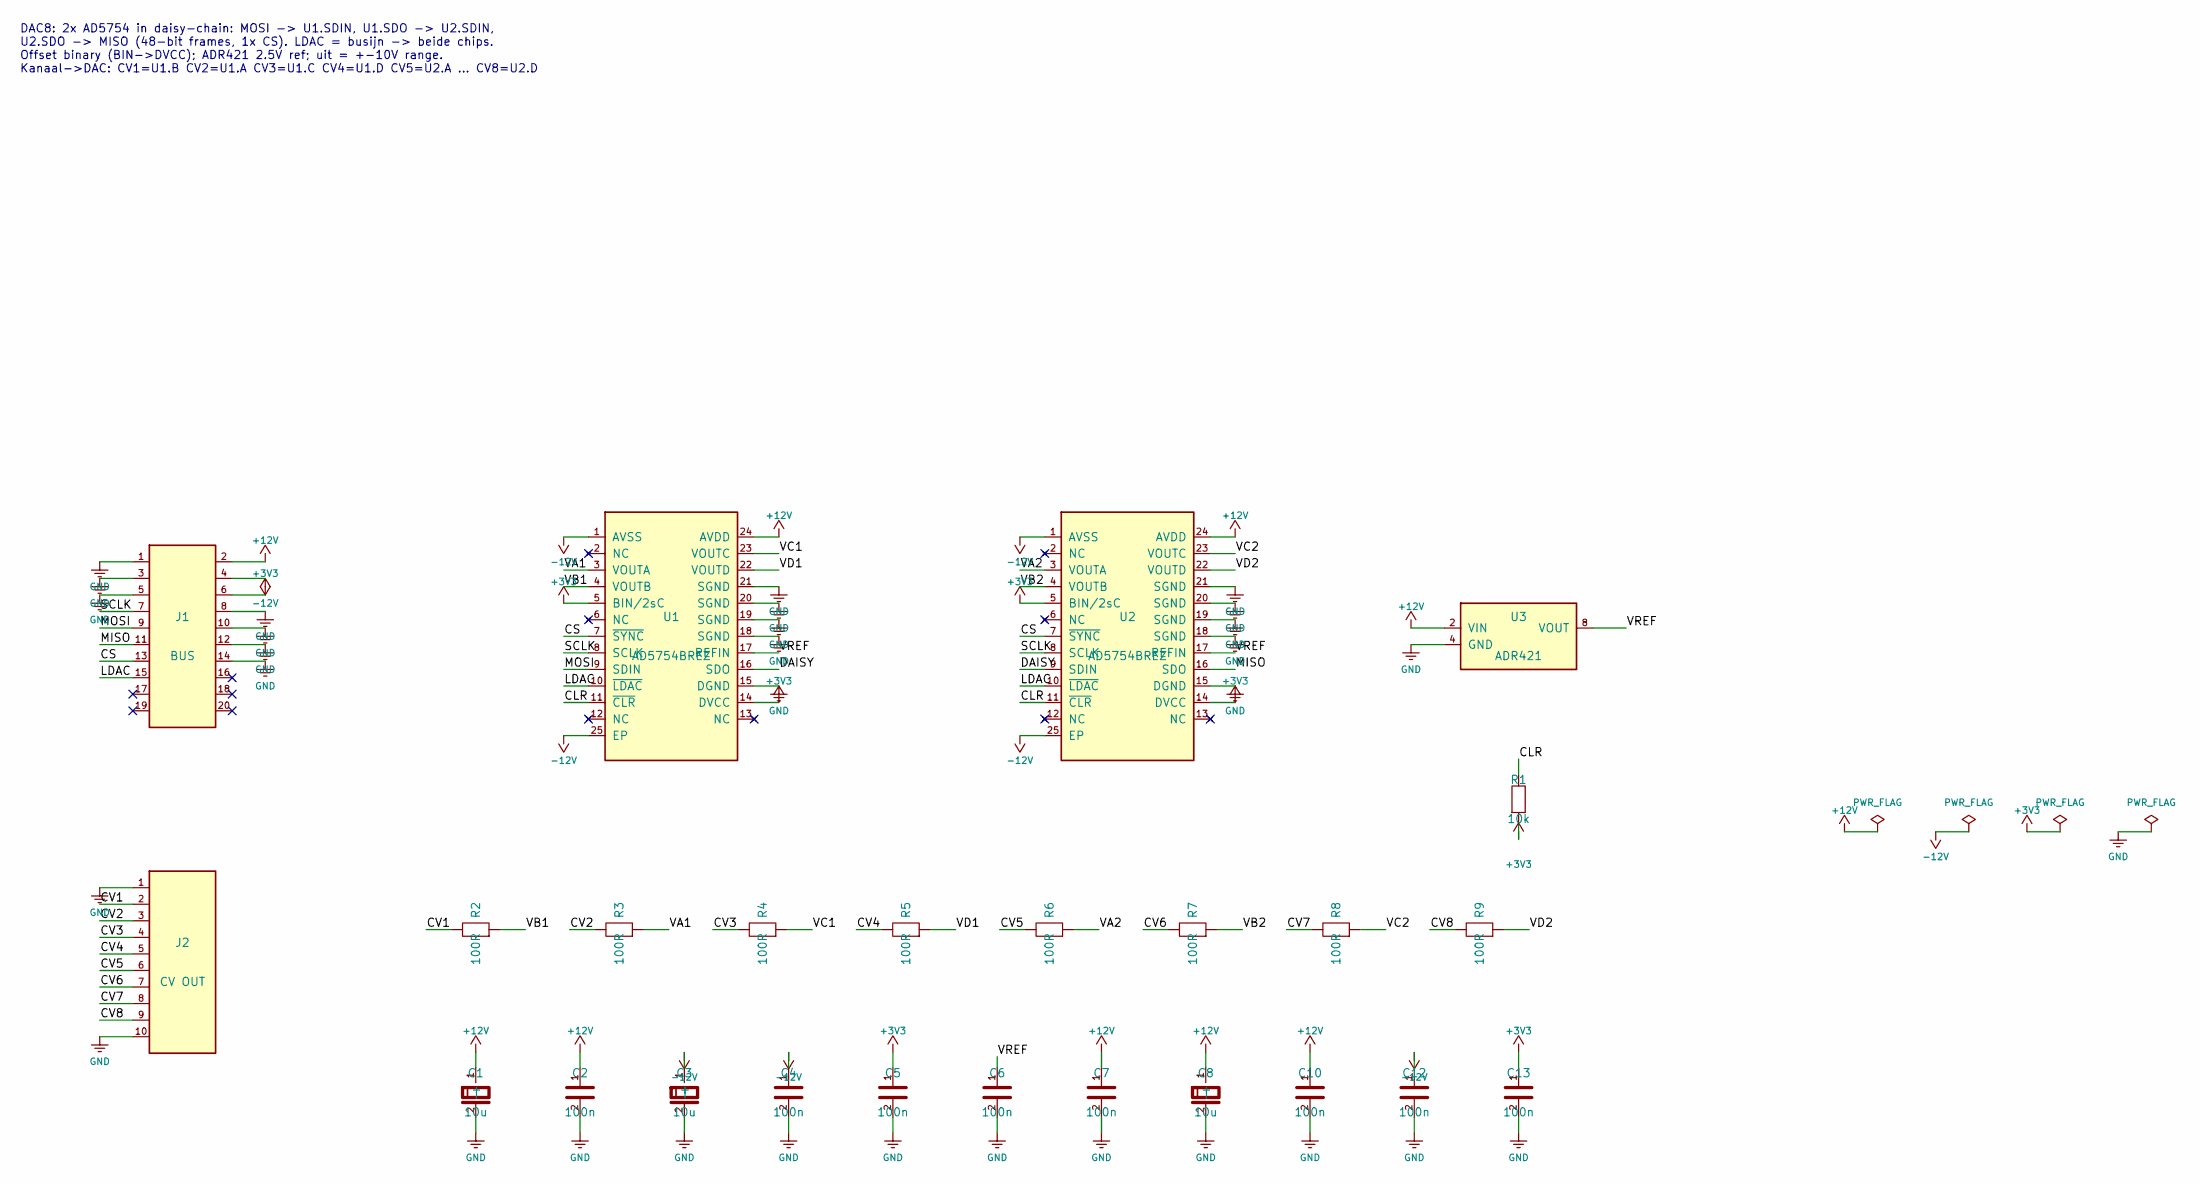
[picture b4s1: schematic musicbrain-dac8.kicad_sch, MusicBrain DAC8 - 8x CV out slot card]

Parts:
C1, C3, C8: 10u; CP_Elec_4x5.3
C2, C4, C5, C6, C7, C10, C12, C13: 100n; C_0805_2012Metric
J1: BUS; PinHeader_2x10_P2.54mm_Horizontal
J2: CV OUT; PinHeader_1x10_P2.54mm_Horizontal
R1: 10k; R_0805_2012Metric
R2, R3, R4, R5, R6, R7, R8, R9: 100R; R_0805_2012Metric
U1, U2: AD5754BREZ; HTSSOP-24-1EP_4.4x7.8mm_P0.65mm_EP3.2x5mm
U3: ADR421; SOIC-8_3.9x4.9mm_P1.27mm

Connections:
+3V3: C5.1, C13.1, J1.6, R1.2, U1.5 (BIN/2sC), U1.14 (DVCC), U2.5 (BIN/2sC), U2.14 (DVCC)
+12V: C1.1 (+), C2.1, C7.1, C8.1 (+), C10.1, J1.2, U1.24 (AVDD), U2.24 (AVDD), U3.2 (VIN)
-12V: C3.1 (+), C4.1, C12.1, J1.4, U1.1 (AVSS), U1.25 (EP), U2.1 (AVSS), U2.25 (EP)
/CLR: R1.1, U1.11 (~CLR), U2.11 (~CLR)
/CS: J1.13, U1.7 (~SYNC), U2.7 (~SYNC)
/CV1: J2.2, R2.1
/CV2: J2.3, R3.1
/CV3: J2.4, R4.1
/CV4: J2.5, R5.1
/CV5: J2.6, R6.1
/CV6: J2.7, R7.1
/CV7: J2.8, R8.1
/CV8: J2.9, R9.1
/DAISY: U1.16 (SDO), U2.9 (SDIN)
/LDAC: J1.15, U1.10 (~LDAC), U2.10 (~LDAC)
/MISO: J1.11, U2.16 (SDO)
/MOSI: J1.9, U1.9 (SDIN)
/SCLK: J1.7, U1.8 (SCLK), U2.8 (SCLK)
/VA1: R3.2, U1.3 (VOUTA)
/VA2: R6.2, U2.3 (VOUTA)
/VB1: R2.2, U1.4 (VOUTB)
/VB2: R7.2, U2.4 (VOUTB)
/VC1: R4.2, U1.23 (VOUTC)
/VC2: R8.2, U2.23 (VOUTC)
/VD1: R5.2, U1.22 (VOUTD)
/VD2: R9.2, U2.22 (VOUTD)
/VREF: C6.1, U1.17 (REFIN), U2.17 (REFIN), U3.8 (VOUT); also elsewhere on the board
GND: C1.2 (-), C2.2, C3.2 (-), C4.2, C5.2, C6.2, C7.2, C8.2 (-), C10.2, C12.2, C13.2, J1.1, J1.3, J1.5, J1.8, J1.10, J1.12, J1.14, J2.1, J2.10, U1.15 (DGND), U1.18 (SGND), U1.19 (SGND), U1.20 (SGND), U1.21 (SGND), U2.15 (DGND), U2.18 (SGND), U2.19 (SGND), U2.20 (SGND), U2.21 (SGND), U3.4 (GND); also elsewhere on the board

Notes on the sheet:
DAC8: 2x AD5754 in daisy-chain: MOSI -> U1.SDIN, U1.SDO -> U2.SDIN, U2.SDO -> MISO (48-bit frames, 1x CS). LDAC = busijn -> beide chips. Offset binary (BIN->DVCC); ADR421 2.5V ref; uit = +-10V range. Kanaal->DAC: CV1=U1.B CV2=U1.A CV3=U1.C CV4=U1.D CV5=U2.A ... CV8=U2.D
